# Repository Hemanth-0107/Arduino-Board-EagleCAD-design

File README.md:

This is a arduino board design using EagleCAD

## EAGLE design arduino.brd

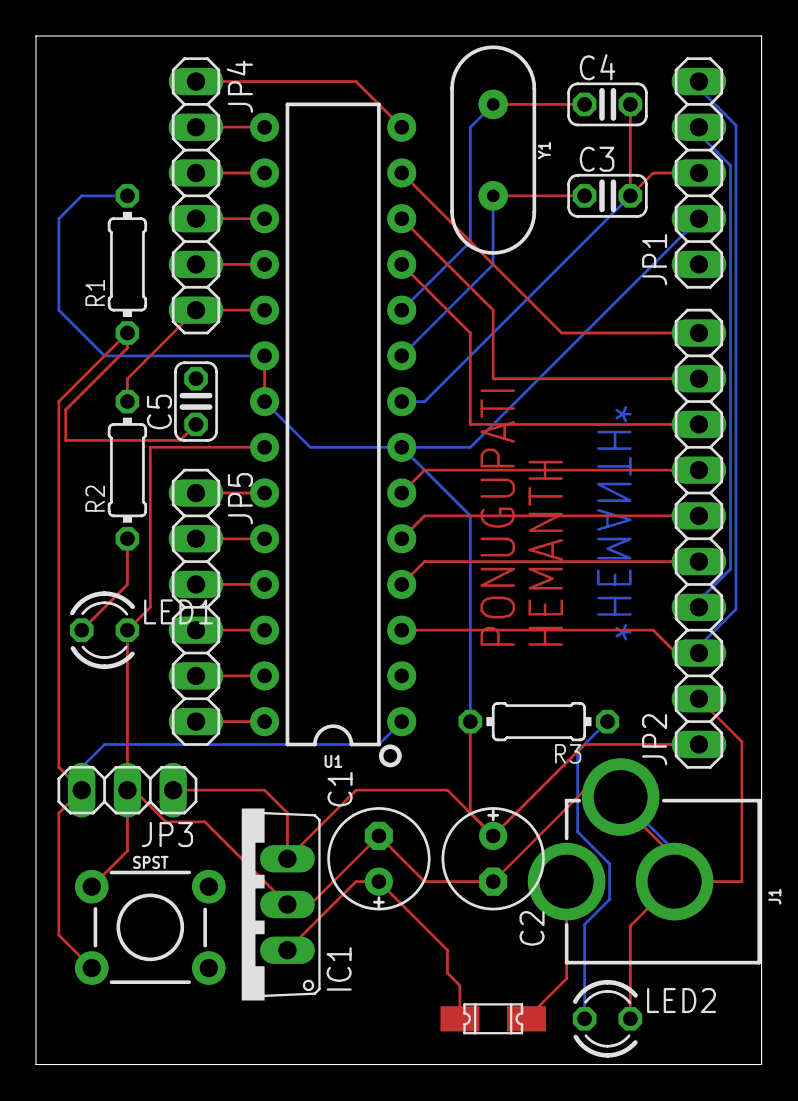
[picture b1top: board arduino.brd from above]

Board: 2 copper layers, 40.3 x 57.1 mm, 21 parts (0 on the bottom side), 30 nets.

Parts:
C1, C2: 10uF; E2,5-6E
C3, C4, C5: 22pF; C025-024X044
F1: 1206L
IC1: 7805TV; TO220V
J1: POWER_JACK; POWER_JACK_PTH
JP1: 1X05
JP2: 1X10
JP3: 1X03
JP4, JP5: 1X06
LED1, LED2: Green; LED3MM
R1: 10K; 0204/7
R2, R3: 220E; 0204/7
SPST: MOMENTARY-SWITCH-SPST-PTH-6.0MM; TACTILE_SWITCH_PTH_6.0MM
U1: 328P; DIP28
Y1: 16MHz; HC49US

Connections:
A0: JP5.1, U1.23
A1: JP5.2, U1.24
A2: JP5.3, U1.25
A3: JP5.4, U1.26
A4: JP5.5, U1.27
A5: JP5.6, U1.28
D2: JP2.5, U1.4
D3: JP2.6, U1.5
D4: JP2.7, U1.6
D5: JP2.8, U1.11
D6: JP2.9, U1.12
D7: JP2.10, U1.13
D8: JP4.1, U1.14
D9: JP4.2, U1.15
D10: JP4.3, U1.16
D11: JP4.4, U1.17
D12: JP4.5, U1.18
D13: JP4.6, R2.2, U1.19
GND: C1.-, C2.-, IC1.2, J1.GND, J1.GNDBREAK, JP2.2, JP3.2, LED1.K, LED2.K, SPST.1, U1.22
unnamed: C1.+, F1.P$2, IC1.1
unnamed: C3.1, U1.9, Y1.2
unnamed: C4.1, U1.10, Y1.1
unnamed: LED2.A, R3.1
unnamed: LED1.A, R2.1
unnamed: F1.P$1, J1.PWR
RESET: C5.1, JP3.3, R1.1, SPST.3, U1.1
RX: JP1.4, JP2.4
S$1: C3.2, C4.2, JP1.3, U1.8
TX: JP1.5, JP2.3, U1.3
VCC: C2.+, IC1.3, JP1.2, JP2.1, JP3.1, R1.2, R3.2, U1.7, U1.20, U1.21

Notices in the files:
parts and their libraries:
SparkFun-Connectors: Licensing: Creative Commons ShareAlike 4.0 International - https://creativecommons.org/licenses/by-sa/4.0
